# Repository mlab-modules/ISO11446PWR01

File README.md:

#  ISO11446PWR01 - Trailer emulator

[ISO 11446 specifies a 13-pole electrical connector](https://en.wikipedia.org/wiki/ISO_standards_for_trailer_connectors#13-pin_trailer_connector_(ISO_11446)) between towing and towed vehicles with 12 volt electrical system. The module emulates connection of the trailer to get power supply and commands signals for connected devices.

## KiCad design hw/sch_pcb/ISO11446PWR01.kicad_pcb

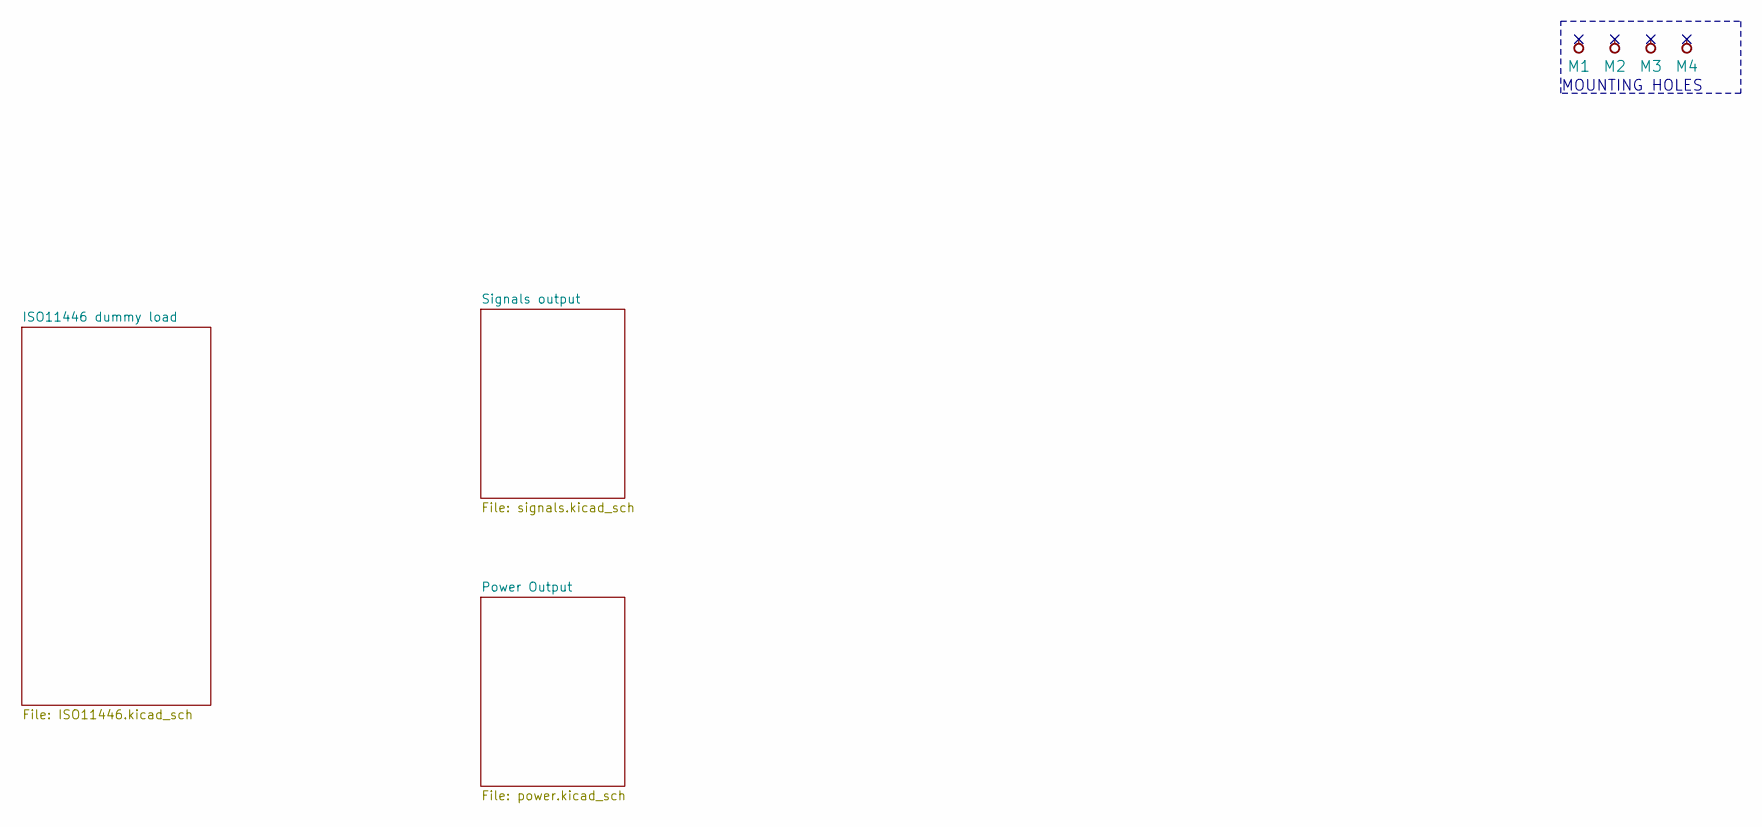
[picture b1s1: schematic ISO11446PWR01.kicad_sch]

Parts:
M1, M2: HOLE M3; MountingHole_3mm
M3, M4: HOLE; MountingHole_3mm

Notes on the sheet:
MOUNTING HOLES

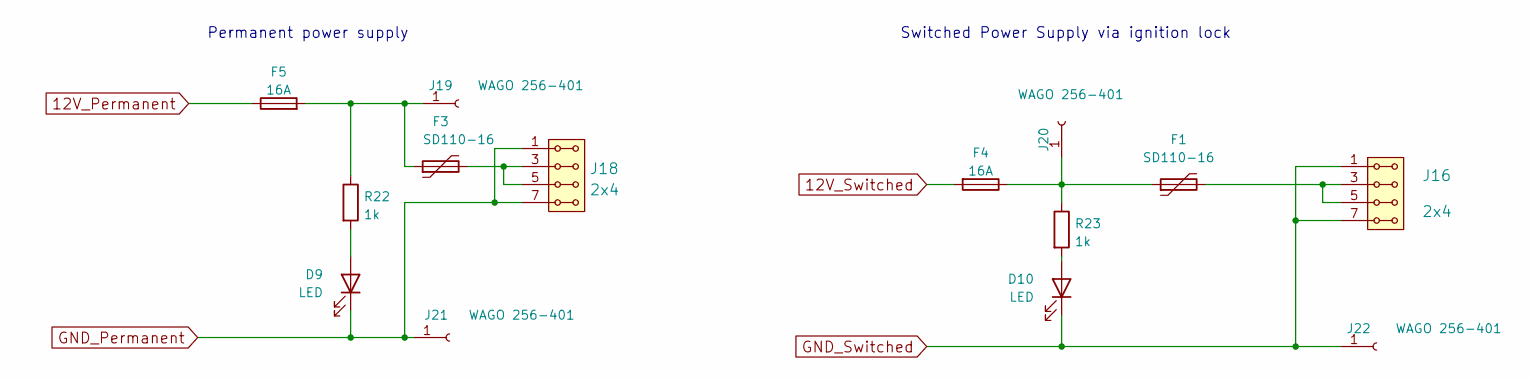
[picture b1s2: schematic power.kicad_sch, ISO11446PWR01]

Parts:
D9, D10: LED; LED_1206
F1, F3: SD110-16; 1812
F4, F5: 16A; Fuse-Keystone-3557-2
J16, J18: 2x4; Straight_2x04
J19, J20, J21, J22: WAGO 256-401; WAGO256
R22, R23: 1k; SMD-0805

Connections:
12V_Permanent: F5.1; also elsewhere on the board
12V_Switched: F4.2; also elsewhere on the board
GND_Permanent: D9.1 (K), J18.1, J18.2, J18.7, J18.8, J21.1; also elsewhere on the board
GND_Switched: D10.1 (K), J16.1, J16.2, J16.7, J16.8, J22.1; also elsewhere on the board
unnamed: D9.2 (A), R22.2
unnamed: D10.2 (A), R23.2
unnamed: F1.1, F4.1, J20.1, R23.1
unnamed: F1.2, J16.3, J16.4, J16.5, J16.6
unnamed: F3.1, F5.2, J19.1, R22.1
unnamed: F3.2, J18.3, J18.4, J18.5, J18.6

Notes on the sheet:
Permanent power supply
Switched Power Supply via ignition lock

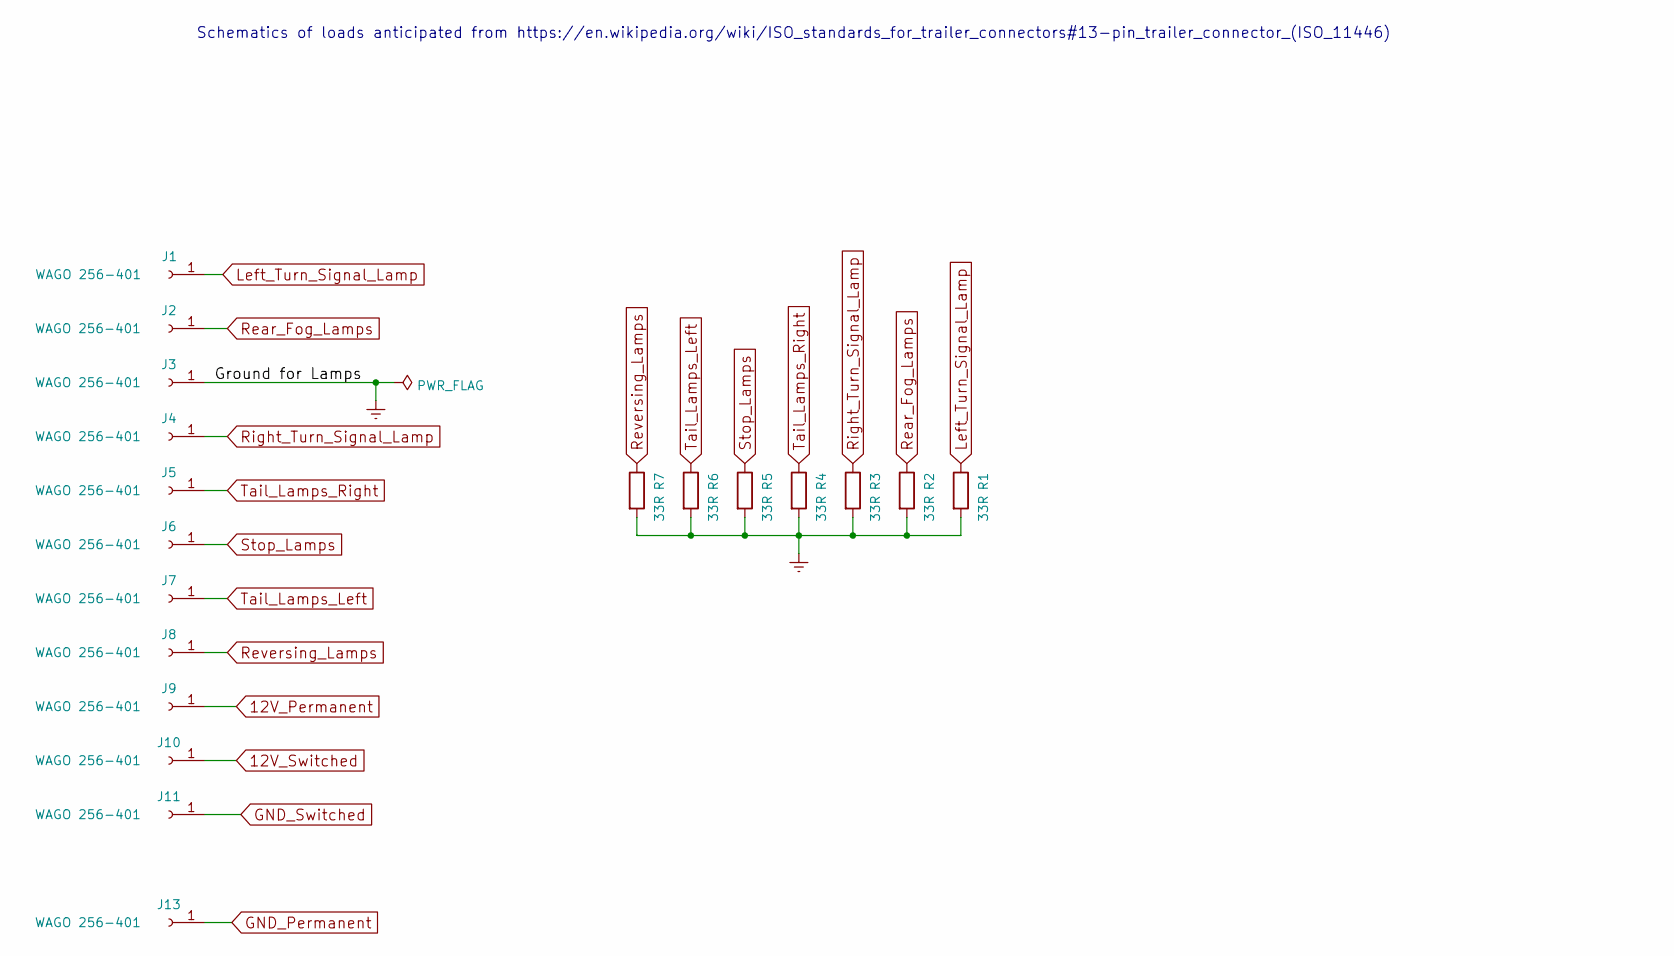
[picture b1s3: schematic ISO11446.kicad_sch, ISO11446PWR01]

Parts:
J1, J2, J3, J4, J5, J6, J7, J8, J9, J10, J11, J13: WAGO 256-401; WAGO256
R1, R2, R3, R4, R5, R6, R7: 33R; R_Radial_Power_L13.0mm_W9.0mm_P5.00mm

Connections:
12V_Permanent: J9.1; also elsewhere on the board
12V_Switched: J10.1; also elsewhere on the board
Earth: J3.1, R1.2, R2.2, R3.2, R4.2, R5.2, R6.2, R7.2; also elsewhere on the board
GND_Permanent: J13.1; also elsewhere on the board
GND_Switched: J11.1; also elsewhere on the board
Left_Turn_Signal_Lamp: J1.1, R1.1; also elsewhere on the board
Rear_Fog_Lamps: J2.1, R2.1; also elsewhere on the board
Reversing_Lamps: J8.1, R7.1; also elsewhere on the board
Right_Turn_Signal_Lamp: J4.1, R3.1; also elsewhere on the board
Stop_Lamps: J6.1, R5.1; also elsewhere on the board
Tail_Lamps_Left: J7.1, R6.1; also elsewhere on the board
Tail_Lamps_Right: J5.1, R4.1; also elsewhere on the board

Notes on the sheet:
Schematics of loads anticipated from https://en.wikipedia.org/wiki/ISO_standards_for_trailer_connectors#13-pin_trailer_connector_(ISO_11446)

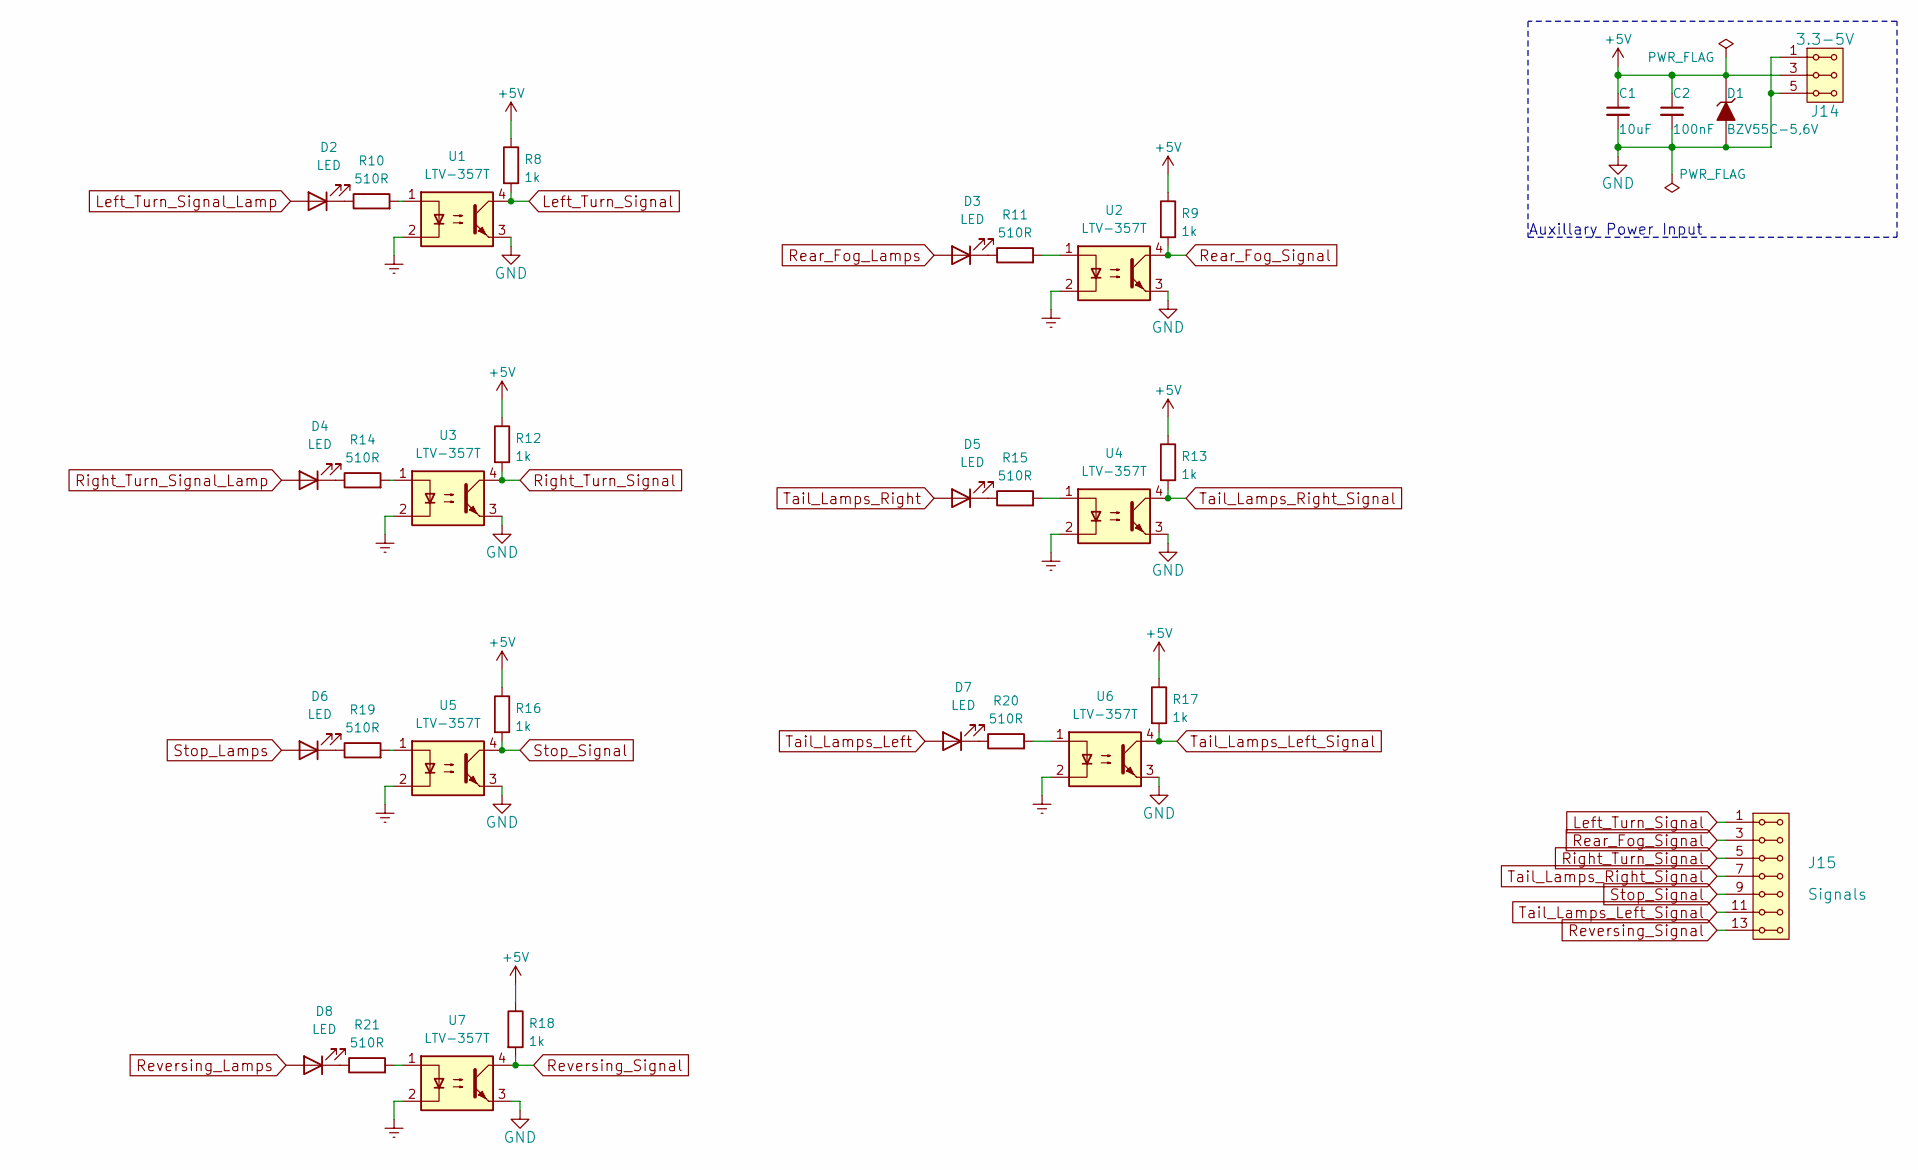
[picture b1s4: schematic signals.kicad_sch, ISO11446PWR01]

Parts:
C1: 10uF; SMD-0805
C2: 100nF; C_0805_2012Metric
D1: BZV55C-5,6V; D_SMA
D2, D3, D4, D5, D6, D7, D8: LED; LED_1206
J14: 3.3-5V; Straight_2x03
J15: Signals; Straight_2x07
R8, R9, R12, R13, R16, R17, R18: 1k; SMD-0805
R10, R11, R14, R15, R19, R20, R21: 510R; SMD-0805
U1, U2, U3, U4, U5, U6, U7: LTV-357T; SO-4_4.4x3.6mm_P2.54mm

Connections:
+5V: C1.1, C2.1, D1.1 (K), J14.3, J14.4, R8.1, R9.1, R12.1, R13.1, R16.1, R17.1, R18.1
Earth: U1.2, U2.2, U3.2, U4.2, U5.2, U6.2, U7.2; also elsewhere on the board
GND: C1.2, C2.2, D1.2 (A), J14.1, J14.2, J14.5, J14.6, U1.3, U2.3, U3.3, U4.3, U5.3, U6.3, U7.3
Left_Turn_Signal: J15.1, J15.2, R8.2, U1.4
Left_Turn_Signal_Lamp: D2.2 (A); also elsewhere on the board
unnamed: D2.1 (K), R10.1
unnamed: D3.1 (K), R11.1
unnamed: D4.1 (K), R14.1
unnamed: D5.1 (K), R15.1
unnamed: D6.1 (K), R19.1
unnamed: D7.1 (K), R20.1
unnamed: D8.1 (K), R21.1
unnamed: R10.2, U1.1
unnamed: R11.2, U2.1
unnamed: R14.2, U3.1
unnamed: R15.2, U4.1
unnamed: R19.2, U5.1
unnamed: R20.2, U6.1
unnamed: R21.2, U7.1
Rear_Fog_Lamps: D3.2 (A); also elsewhere on the board
Rear_Fog_Signal: J15.3, J15.4, R9.2, U2.4
Reversing_Lamps: D8.2 (A); also elsewhere on the board
Reversing_Signal: J15.13, J15.14, R18.2, U7.4
Right_Turn_Signal: J15.5, J15.6, R12.2, U3.4
Right_Turn_Signal_Lamp: D4.2 (A); also elsewhere on the board
Stop_Lamps: D6.2 (A); also elsewhere on the board
Stop_Signal: J15.9, J15.10, R16.2, U5.4
Tail_Lamps_Left: D7.2 (A); also elsewhere on the board
Tail_Lamps_Left_Signal: J15.11, J15.12, R17.2, U6.4
Tail_Lamps_Right: D5.2 (A); also elsewhere on the board
Tail_Lamps_Right_Signal: J15.7, J15.8, R13.2, U4.4

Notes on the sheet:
Auxillary Power Input

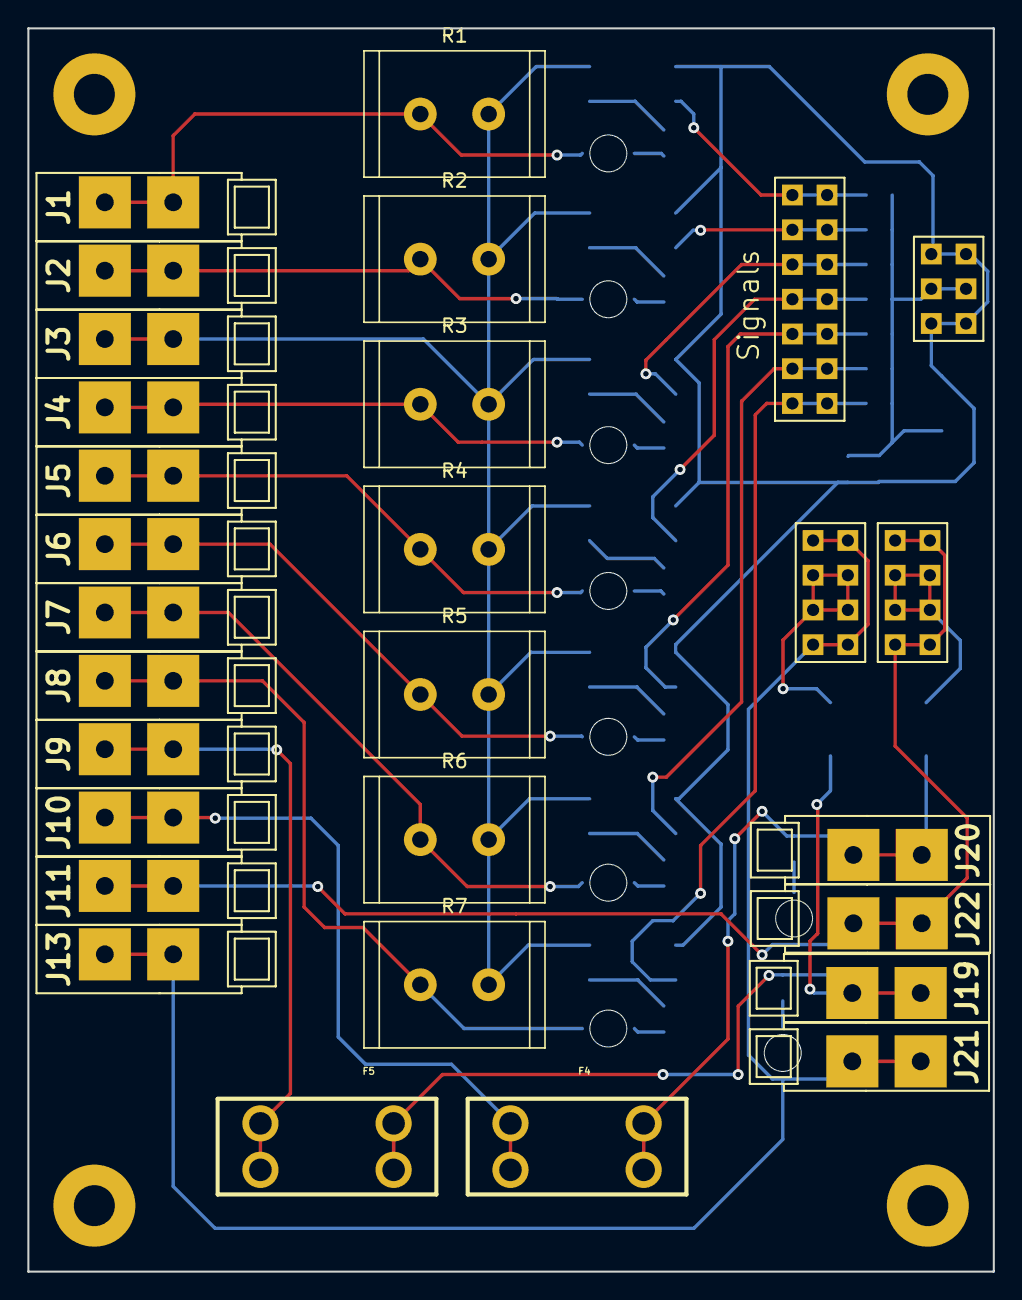
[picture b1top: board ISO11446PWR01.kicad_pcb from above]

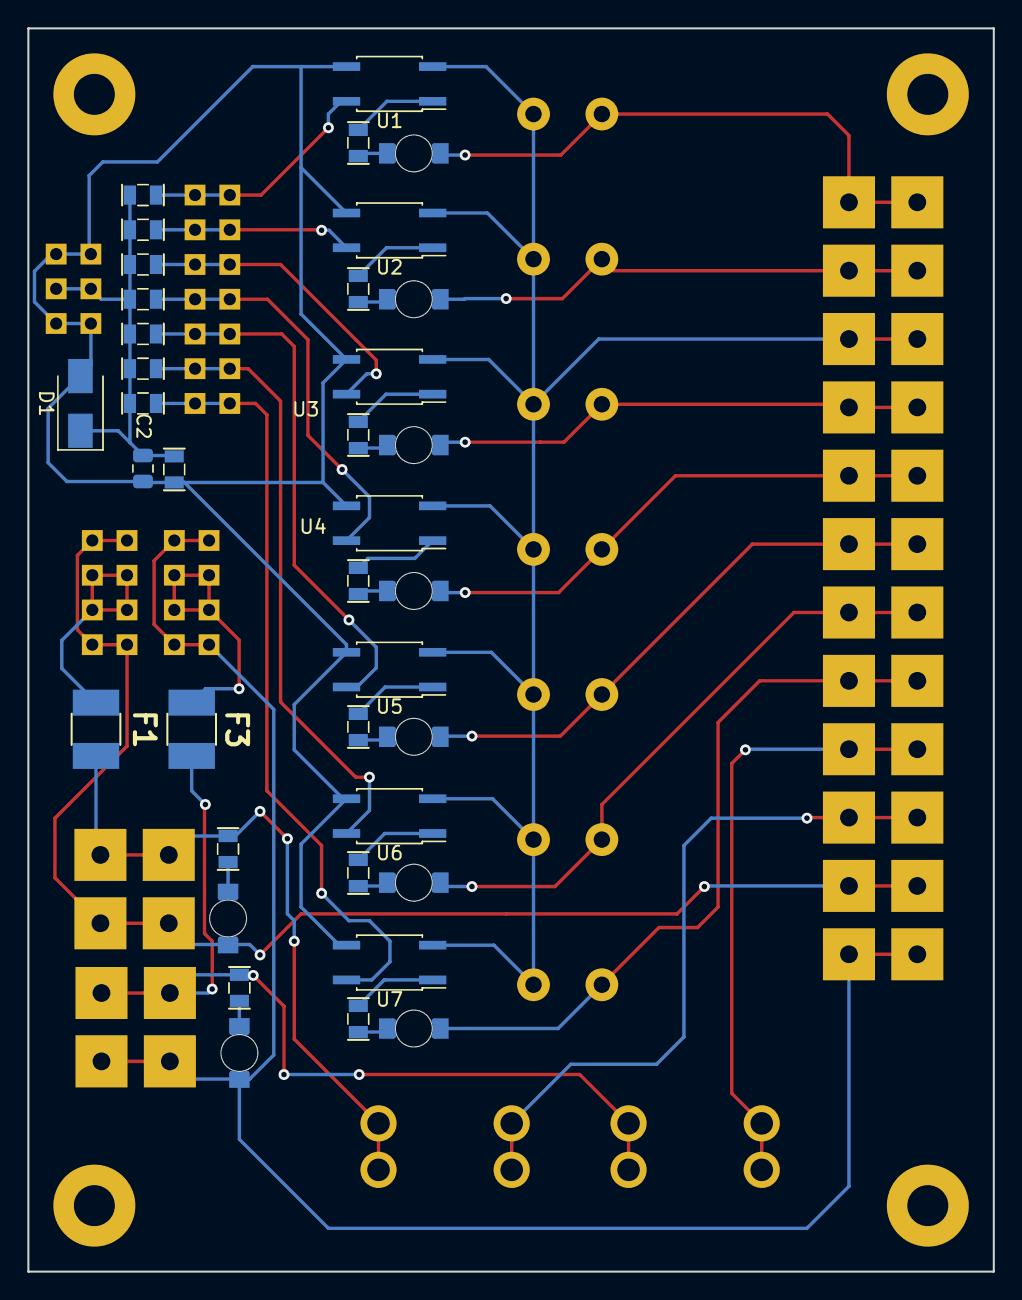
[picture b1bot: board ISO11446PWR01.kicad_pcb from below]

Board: 2 copper layers, 70.6 x 90.9 mm, 70 parts (37 on the bottom side), 41 nets.

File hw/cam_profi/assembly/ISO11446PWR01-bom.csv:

Component,Description,Part,References,Value,Footprint,Quantity Per PCB,Datasheet,ust_id
1,,C_Small-Device-ISM02A-rescue,C2,100nF,C_0805_2012Metric,1,,5c70984812875079b91f8bf2
2,,C_Small-Device-ISM02A-rescue,C1,10uF,SMD-0805,1,,5c70984812875079b91f8bbe
3,,D_ZENER-MLAB_D,D1,"BZV55C-5,6V",D_SMA,1,,5c70984512875079b91f88b2
4,Light emitting diode,LED,D2D3D4D5D6D7D8D9D10,LED,LED_1206,9,~,
5,Fuse,Fuse,F4F5,16A,Fuse-Keystone-3557-2,2,https://www.tme.eu/cz/details/keys3557-2/automobilni-pojistk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,
6,"Resettable fuse, polymeric positive temperature coefficient",Polyfuse,F1F3,SD110-16,1812,2,~,
7,"2x04 2.54 mm pitch header, 2 pins next to each other are connected",HEADER_2x04_PARALLEL,J16J18,2x4,Straight_2x04,2,,
8,"2x03 2.54 mm pitch header, 2 pins next to each other are connected",HEADER_2x03_PARALLEL,J14,3.3-5V,Straight_2x03,1,,
9,"2x07 2.54 mm pitch header, 2 pins next to each other are connected",HEADER_2x07_PARALLEL,J15,Signals,Straight_2x07,1,,
10,"Generic connector, single row, 01x01, script generated (kicad-library-utils/schlib/autogen/connector/)",Conn_01x01_Female,J1J2J3J4J5J6J7J8J9J10J11J13J19J20J21J22,WAGO 256-401,WAGO256,16,~,
11,Resistor,R,R1R2R3R4R5R6R7,33R,R_Radial_Power_L13.0mm_W9.0mm_P5.00mm,7,~,
12,Resistor,R,R10R11R14R15R19R20R21,510R,SMD-0805,7,~,
13,Resistor,R,R8R9R12R13R16R17R18R22R23,1k,SMD-0805,9,~,
14,"DC Optocoupler, Vce 35V, CTR 50%, SO-4",LTV-357T,U1U2U3U4U5U6U7,LTV-357T,SO-4_4.4x3.6mm_P2.54mm,7,https://www.buerklin.com/medias/sys_master/download/download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,5c70984412875079b91f8789

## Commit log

2023-02-09 init workflow
2023-02-09 create kicad project
2023-02-09 testing schema
2023-02-10 Update workflow files
2023-02-10 Update actions products
2023-02-12 Update metadata files
2023-02-16 An initial test implementation. Both Schema and PCB needs check.
2023-02-16 slove some warnings.
2023-02-16 Improve layout and connector orientation.
2023-02-16 drobne upravy schematu
2023-02-20 Significant schematic and layout improvement. Fixed fuse footprint Fixed schematics * Spliting to multiple sheets * Texts translated from czech to english
2023-05-28 automated commit; add github actions
2023-07-05 automated commit; rename source files to new naming convence
2023-09-16 Update image to image_title
2023-09-16 Update status
2026-02-14 Update to KiCADv9.
2026-03-07 Interview task submission
